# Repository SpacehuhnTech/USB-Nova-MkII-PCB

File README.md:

# USB-Nova-MkII-PCB

USB Nova MkII Hardware Design Files

USB Nova is a cute little USB “drive” that acts as a keyboard, much like the USB Rubber Ducky, WiFi Duck, and other BadUSBs. 

This is the USB-C version.

Learn about the Project at [usbnova.com](https://usbnova.com).  
Buy one at [spacehuhn.store](https://spacehuhn.store/products/usb-nova).

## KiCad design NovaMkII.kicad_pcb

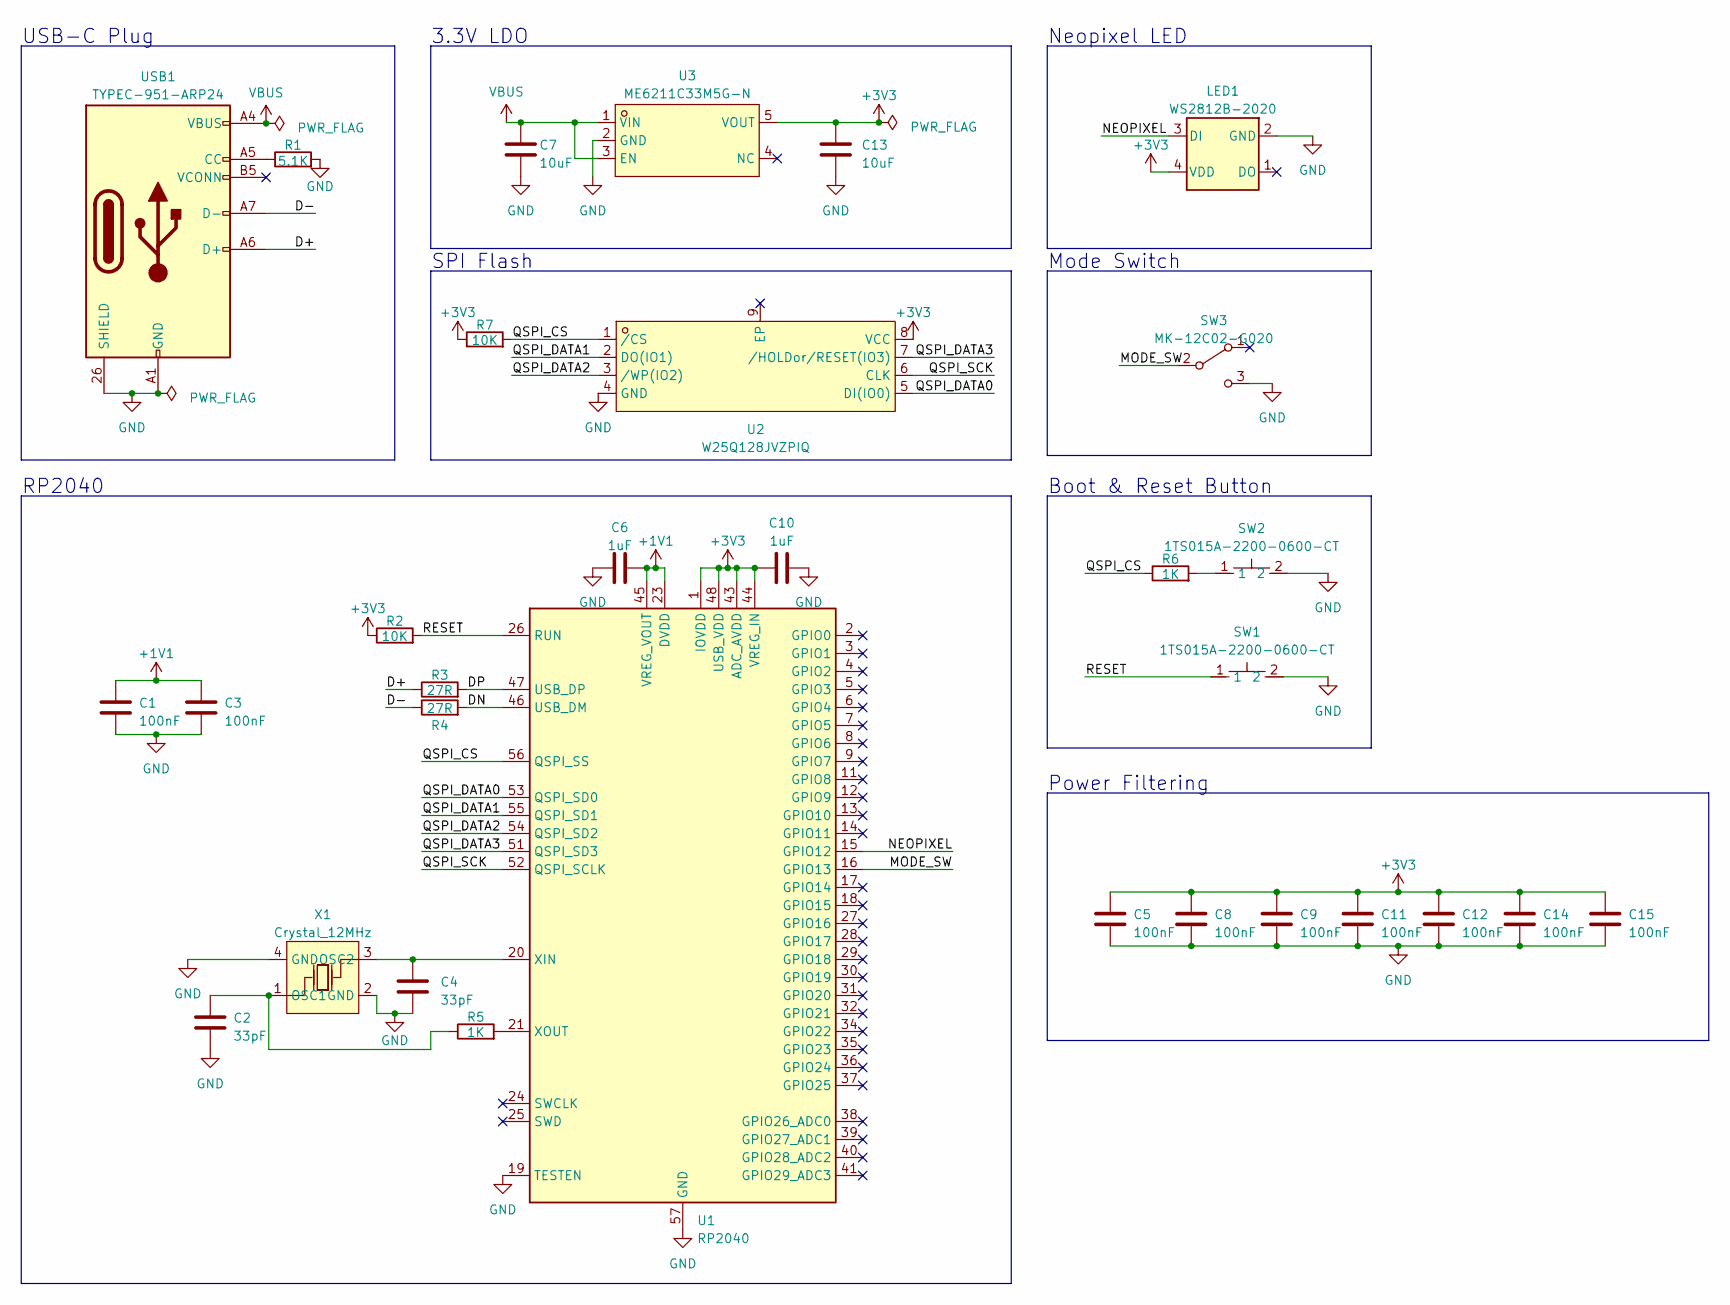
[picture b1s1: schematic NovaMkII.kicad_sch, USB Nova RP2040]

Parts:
C1, C3, C5, C8, C9, C11, C12, C14, C15: 100nF; C_0402_1005Metric
C2, C4: 33pF; C_0402_1005Metric
C6, C10: 1uF; C_0603_1608Metric
C7, C13: 10uF; C_0603_1608Metric
LED1: WS2812B-2020; LED-SMD_4P-L2.0-W2.0-TL_WS2812B-2020; MPN C965555
R1: 5.1K; R_0402_1005Metric
R2, R7: 10K; R_0402_1005Metric
R3, R4: 27R; R_0402_1005Metric; MPN C2909343
R5, R6: 1K; R_0402_1005Metric
SW1, SW2: 1TS015A-2200-0600-CT; SW-SMD_L3.0-W2.0-LS3.5; MPN C398748
SW3: MK-12C02-G020; SW_MK-12C02-G020; MPN C963206
U1: RP2040; QFN-56-1EP_7x7mm_P0.4mm_EP3.2x3.2mm; MPN C2040
U2: W25Q128JVZPIQ; WSON-8_L6.0-W5.0-P1.27-BL-EP; MPN C190862
U3: ME6211C33M5G-N; SOT-25-5_ME6211C33M5G; MPN C82942
USB1: TYPEC-951-ARP24; USB-C-SMD_TYPEC-951-ARP24; MPN C2856663
X1: Crystal_12MHz; OSC-SMD_4P-L3.2-W2.5-BL; MPN C9002

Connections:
+1V1: C1.1, C3.1, C6.2, U1.23 (DVDD), U1.45 (VREG_VOUT), U1.50 (DVDD)
+3V3: C5.1, C8.1, C9.1, C10.1, C11.1, C12.1, C13.1, C14.1, C15.1, LED1.4 (VDD), R2.1, R7.1, U1.1 (IOVDD), U1.10 (IOVDD), U1.22 (IOVDD), U1.33 (IOVDD), U1.42 (IOVDD), U1.43 (ADC_AVDD), U1.44 (VREG_IN), U1.48 (USB_VDD), U1.49 (IOVDD), U2.8 (VCC), U3.5 (VOUT)
/D+: R3.1, USB1.A6 (D+)
/D-: R4.1, USB1.A7 (D-)
/DN: R4.2, U1.46 (USB_DM)
/DP: R3.2, U1.47 (USB_DP)
/MODE_SW: SW3.2 (B), U1.16 (GPIO13)
/NEOPIXEL: LED1.3 (DI), U1.15 (GPIO12)
/QSPI_CS: R6.1, R7.2, U1.56 (QSPI_SS), U2.1 (/CS)
/QSPI_DATA0: U1.53 (QSPI_SD0), U2.5 (DI(IO0))
/QSPI_DATA1: U1.55 (QSPI_SD1), U2.2 (DO(IO1))
/QSPI_DATA2: U1.54 (QSPI_SD2), U2.3 (/WP(IO2))
/QSPI_DATA3: U1.51 (QSPI_SD3), U2.7 (/HOLDor/RESET(IO3))
/QSPI_SCK: U1.52 (QSPI_SCLK), U2.6 (CLK)
/RESET: R2.2, SW1.1, U1.26 (RUN)
GND: C1.2, C2.2, C3.2, C4.2, C5.2, C6.1, C7.1, C8.2, C9.2, C10.2, C11.2, C12.2, C13.2, C14.2, C15.2, LED1.2 (GND), R1.2, SW1.2, SW2.2, SW3.3 (C), U1.19 (TESTEN), U1.57 (GND), U2.4 (GND), U3.2 (GND), USB1.25 (SHIELD), USB1.26 (SHIELD), USB1.A1 (GND), USB1.A12 (GND), USB1.B1 (GND), USB1.B12 (GND), X1.2 (GND), X1.4 (GND)
unnamed: R6.2, SW2.1
unnamed: C4.1, U1.20 (XIN), X1.3 (OSC2)
unnamed: R5.2, U1.21 (XOUT)
unnamed: R1.1, USB1.A5 (CC)
unnamed: C2.1, R5.1, X1.1 (OSC1)
VBUS: C7.2, U3.1 (VIN), U3.3 (EN), USB1.A4 (VBUS), USB1.A9 (VBUS), USB1.B4 (VBUS), USB1.B9 (VBUS)

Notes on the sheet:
USB-C Plug
SPI Flash
Neopixel LED
Power Filtering
Mode Switch
RP2040
3.3V LDO
Boot & Reset Button

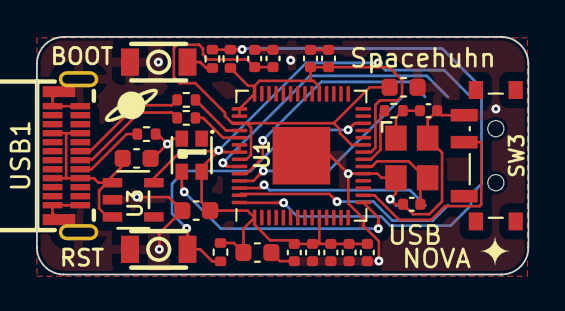
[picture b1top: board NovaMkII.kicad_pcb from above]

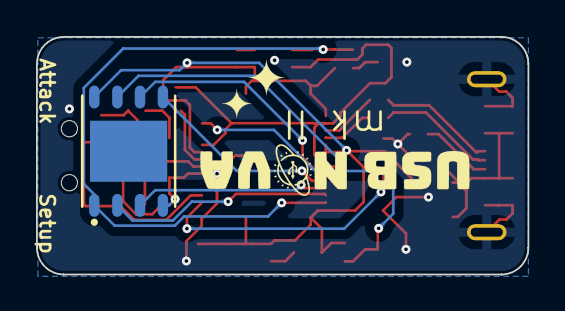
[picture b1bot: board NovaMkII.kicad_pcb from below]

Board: 2 copper layers, 27.3 x 13.2 mm, 36 parts (4 on the bottom side), 22 nets.

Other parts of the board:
G1: LOGO; nova
G4: LOGO; star_small
G5, G8: LOGO; star_tiny
G6: LOGO; planet_small

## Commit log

2023-06-29 Added files
